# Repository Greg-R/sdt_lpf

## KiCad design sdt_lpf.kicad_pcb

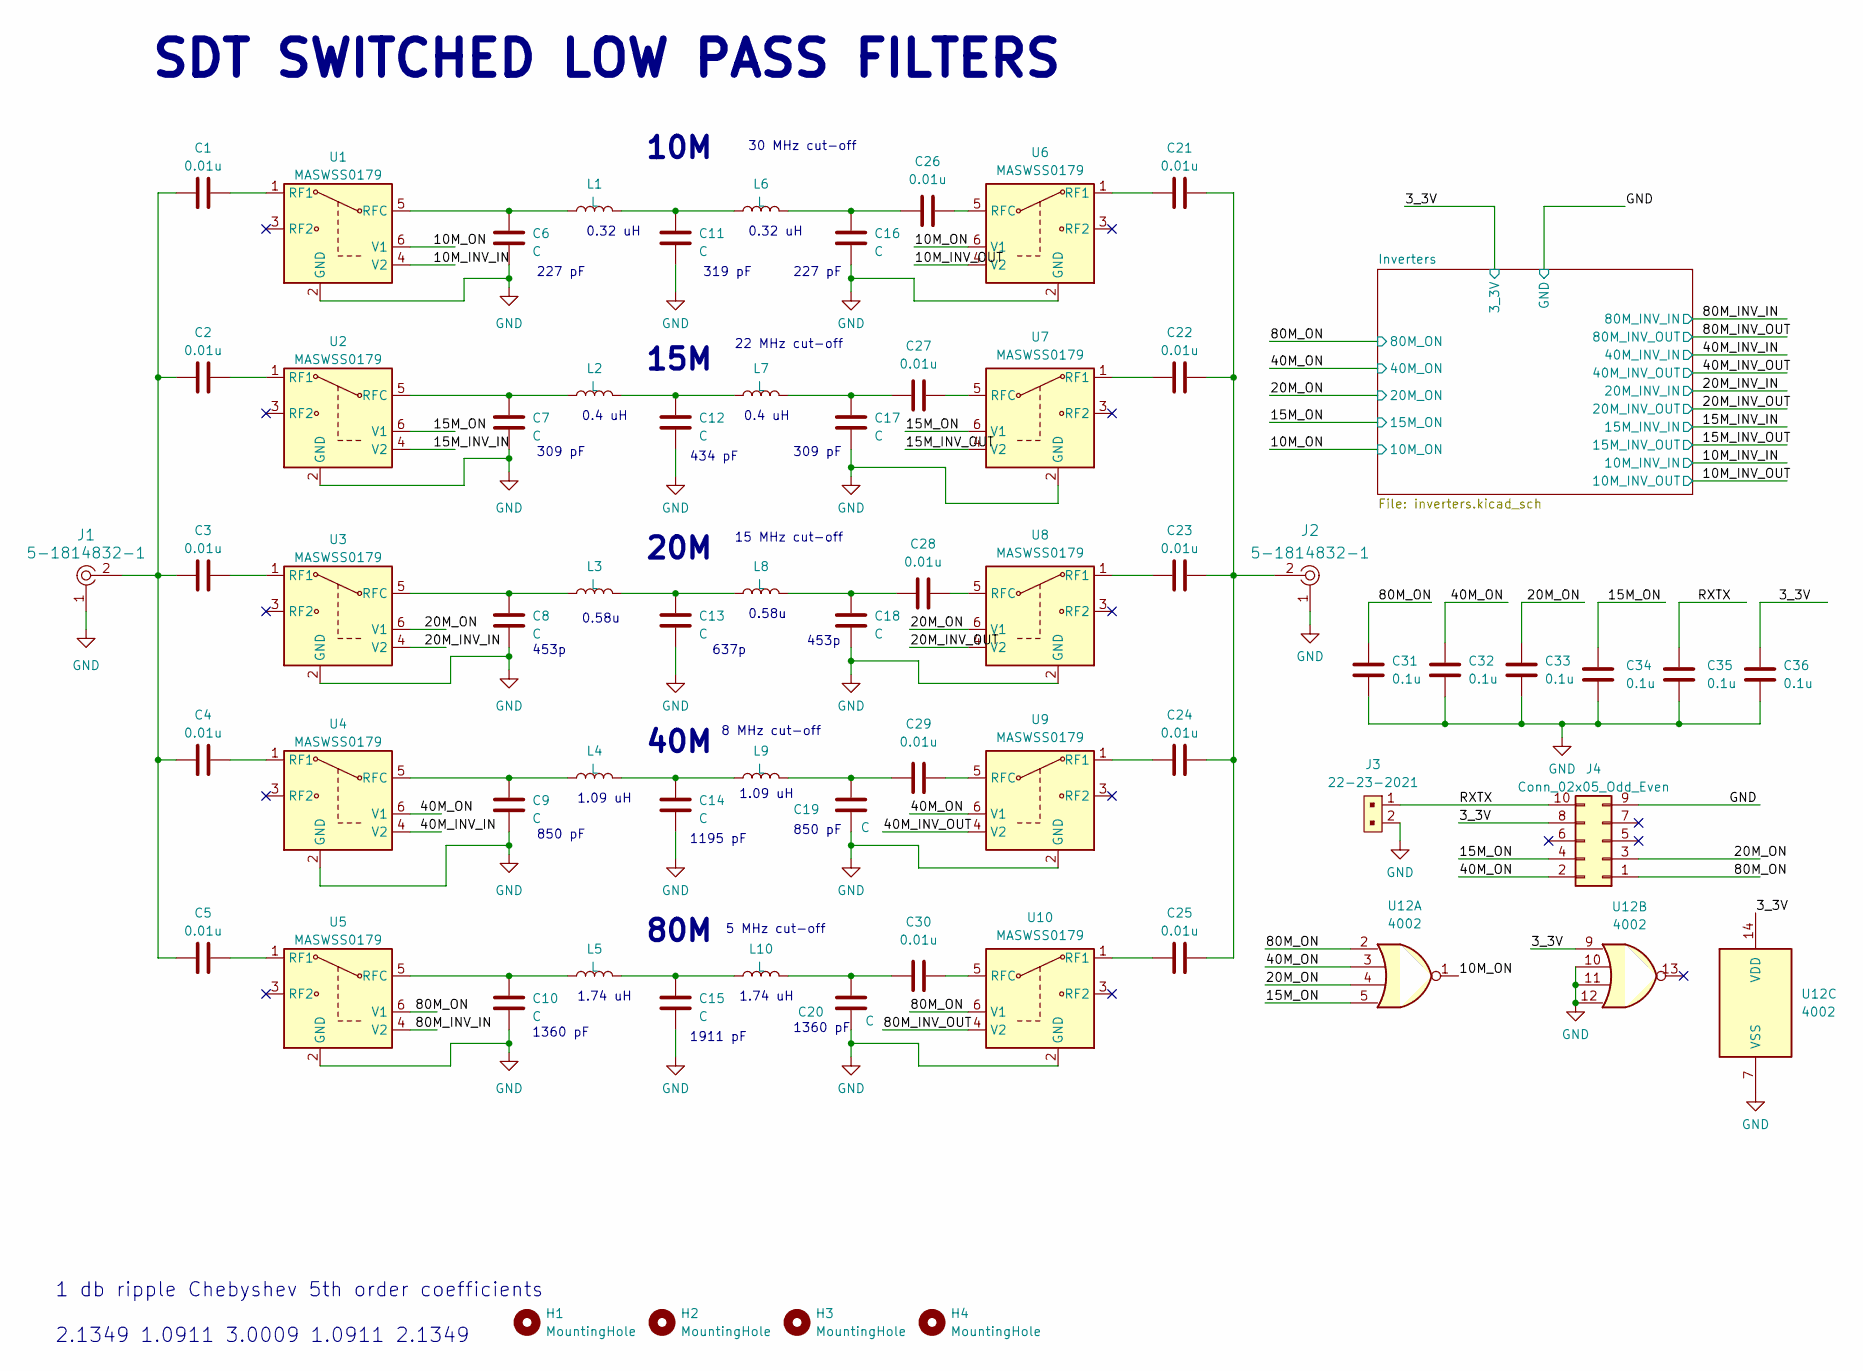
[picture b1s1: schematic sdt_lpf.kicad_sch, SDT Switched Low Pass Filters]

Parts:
C1, C2, C3, C4, C5, C21, C22, C23, C24, C25, C26, C27, C28, C29, C30: 0.01u; C_1206_3216Metric
C6, C7, C8, C9, C10, C11, C12, C13, C14, C15, C16, C17, C18, C19, C20: C; C_1206_3216Metric
C31, C32, C33, C34, C35, C36: 0.1u; C_1206_3216Metric
H1, H2, H3, H4: MountingHole; MountingHole_3.2mm_M3
J1, J2: 5-1814832-1; RF_SMA_Vertical_5-1814832-1; MPN 5-1814832-1; Digi-Key_PN A97594-ND
J3: 22-23-2021; PinHeader_1x2_P2.54mm_Drill1.02mm; MPN 22-23-2021; Digi-Key_PN WM4200-ND
J4: Conn_02x05_Odd_Even; IDC-Header_2x05_P2.54mm_Vertical
L1, L2, L3, L4, L5, L6, L7, L8, L9, L10: L; Toroid_SMD
U1, U2, U3, U4, U5, U6, U7, U8, U9, U10: MASWSS0179; SOT-23-6
U12: 4002; SOIC-14_3.9x8.7mm_P1.27mm

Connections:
/3_3V: C36.2, J4.8, U12.9, U12.14 (VDD); also elsewhere on the board
/10M_INV_IN: U1.4 (V2); also elsewhere on the board
/10M_INV_OUT: U6.4 (V2); also elsewhere on the board
/10M_ON: U1.6 (V1), U6.6 (V1), U12.1; also elsewhere on the board
/15M_INV_IN: U2.4 (V2); also elsewhere on the board
/15M_INV_OUT: U7.4 (V2); also elsewhere on the board
/15M_ON: C34.2, J4.4, U2.6 (V1), U7.6 (V1), U12.5; also elsewhere on the board
/20M_INV_IN: U3.4 (V2); also elsewhere on the board
/20M_INV_OUT: U8.4 (V2); also elsewhere on the board
/20M_ON: C33.2, J4.3, U3.6 (V1), U8.6 (V1), U12.4; also elsewhere on the board
/40M_INV_IN: U4.4 (V2); also elsewhere on the board
/40M_INV_OUT: U9.4 (V2); also elsewhere on the board
/40M_ON: C32.2, J4.2, U4.6 (V1), U9.6 (V1), U12.3; also elsewhere on the board
/80M_INV_IN: U5.4 (V2); also elsewhere on the board
/80M_INV_OUT: U10.4 (V2); also elsewhere on the board
/80M_ON: C31.2, J4.1, U5.6 (V1), U10.6 (V1), U12.2; also elsewhere on the board
/RXTX: C35.2, J3.1, J4.10
GND: C6.2, C7.2, C8.2, C9.2, C10.2, C11.2, C12.2, C13.2, C14.2, C15.2, C16.2, C17.2, C18.2, C19.2, C20.2, C31.1, C32.1, C33.1, C34.1, C35.1, C36.1, J1.1, J2.1, J3.2, J4.9, U1.2 (GND), U2.2 (GND), U3.2 (GND), U4.2 (GND), U5.2 (GND), U6.2 (GND), U7.2 (GND), U8.2 (GND), U9.2 (GND), U10.2 (GND), U12.7 (VSS), U12.10, U12.11, U12.12; also elsewhere on the board
unnamed: C1.1, C2.1, C3.1, C4.1, C5.1, J1.2
unnamed: C11.1, L1.2, L6.1
unnamed: C12.1, L2.2, L7.1
unnamed: C13.1, L3.2, L8.1
unnamed: C14.1, L4.2, L9.1
unnamed: C15.1, L5.2, L10.1
unnamed: C16.1, C26.1, L6.2
unnamed: C17.1, C27.1, L7.2
unnamed: C18.1, C28.1, L8.2
unnamed: C19.1, C29.1, L9.2
unnamed: C20.1, C30.1, L10.2
unnamed: C21.2, C22.2, C23.2, C24.2, C25.2, J2.2
unnamed: C1.2, U1.1 (RF1)
unnamed: C6.1, L1.1, U1.5 (RFC)
unnamed: C2.2, U2.1 (RF1)
unnamed: C7.1, L2.1, U2.5 (RFC)
unnamed: C3.2, U3.1 (RF1)
unnamed: C8.1, L3.1, U3.5 (RFC)
unnamed: C4.2, U4.1 (RF1)
unnamed: C9.1, L4.1, U4.5 (RFC)
unnamed: C5.2, U5.1 (RF1)
unnamed: C10.1, L5.1, U5.5 (RFC)
unnamed: C21.1, U6.1 (RF1)
unnamed: C26.2, U6.5 (RFC)
unnamed: C22.1, U7.1 (RF1)
unnamed: C27.2, U7.5 (RFC)
unnamed: C23.1, U8.1 (RF1)
unnamed: C28.2, U8.5 (RFC)
unnamed: C24.1, U9.1 (RF1)
unnamed: C29.2, U9.5 (RFC)
unnamed: C25.1, U10.1 (RF1)
unnamed: C30.2, U10.5 (RFC)

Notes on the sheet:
227 pF
637p
1911 pF
1.09 uH
0.32 uH
309 pF
850 pF
0.4 uH
8 MHz cut-off
0.58u
40M
SDT SWITCHED LOW PASS FILTERS
15M
5 MHz cut-off
1 db ripple Chebyshev 5th order coefficients 2.1349 1.0911 3.0009 1.0911 2.1349
22 MHz cut-off
453p
15 MHz cut-off
80M
20M
30 MHz cut-off
1195 pF
1.74 uH
10M
1360 pF
319 pF
434 pF

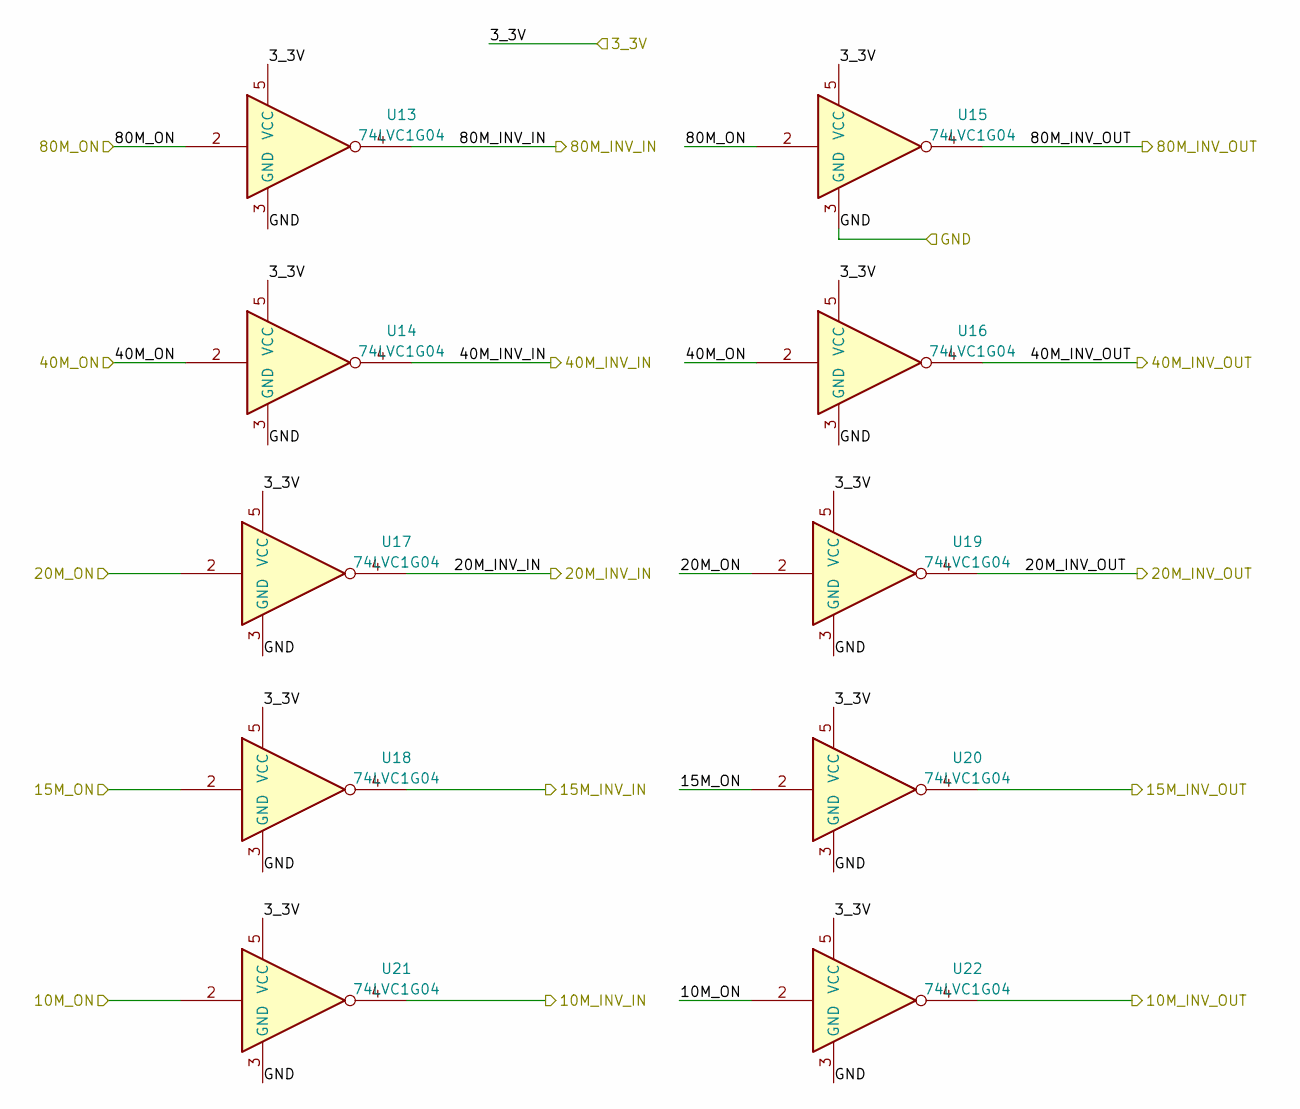
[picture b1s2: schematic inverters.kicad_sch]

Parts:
U13, U14, U15, U16, U17, U18, U19, U20, U21, U22: 74LVC1G04; SOT-353

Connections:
/3_3V: U13.5 (VCC), U14.5 (VCC), U15.5 (VCC), U16.5 (VCC), U17.5 (VCC), U18.5 (VCC), U19.5 (VCC), U20.5 (VCC), U21.5 (VCC), U22.5 (VCC); also elsewhere on the board
/10M_INV_IN: U21.4; also elsewhere on the board
/10M_INV_OUT: U22.4; also elsewhere on the board
/10M_ON: U21.2, U22.2; also elsewhere on the board
/15M_INV_IN: U18.4; also elsewhere on the board
/15M_INV_OUT: U20.4; also elsewhere on the board
/15M_ON: U18.2, U20.2; also elsewhere on the board
/20M_INV_IN: U17.4; also elsewhere on the board
/20M_INV_OUT: U19.4; also elsewhere on the board
/20M_ON: U17.2, U19.2; also elsewhere on the board
/40M_INV_IN: U14.4; also elsewhere on the board
/40M_INV_OUT: U16.4; also elsewhere on the board
/40M_ON: U14.2, U16.2; also elsewhere on the board
/80M_INV_IN: U13.4; also elsewhere on the board
/80M_INV_OUT: U15.4; also elsewhere on the board
/80M_ON: U13.2, U15.2; also elsewhere on the board
GND: U13.3 (GND), U14.3 (GND), U15.3 (GND), U16.3 (GND), U17.3 (GND), U18.3 (GND), U19.3 (GND), U20.3 (GND), U21.3 (GND), U22.3 (GND); also elsewhere on the board

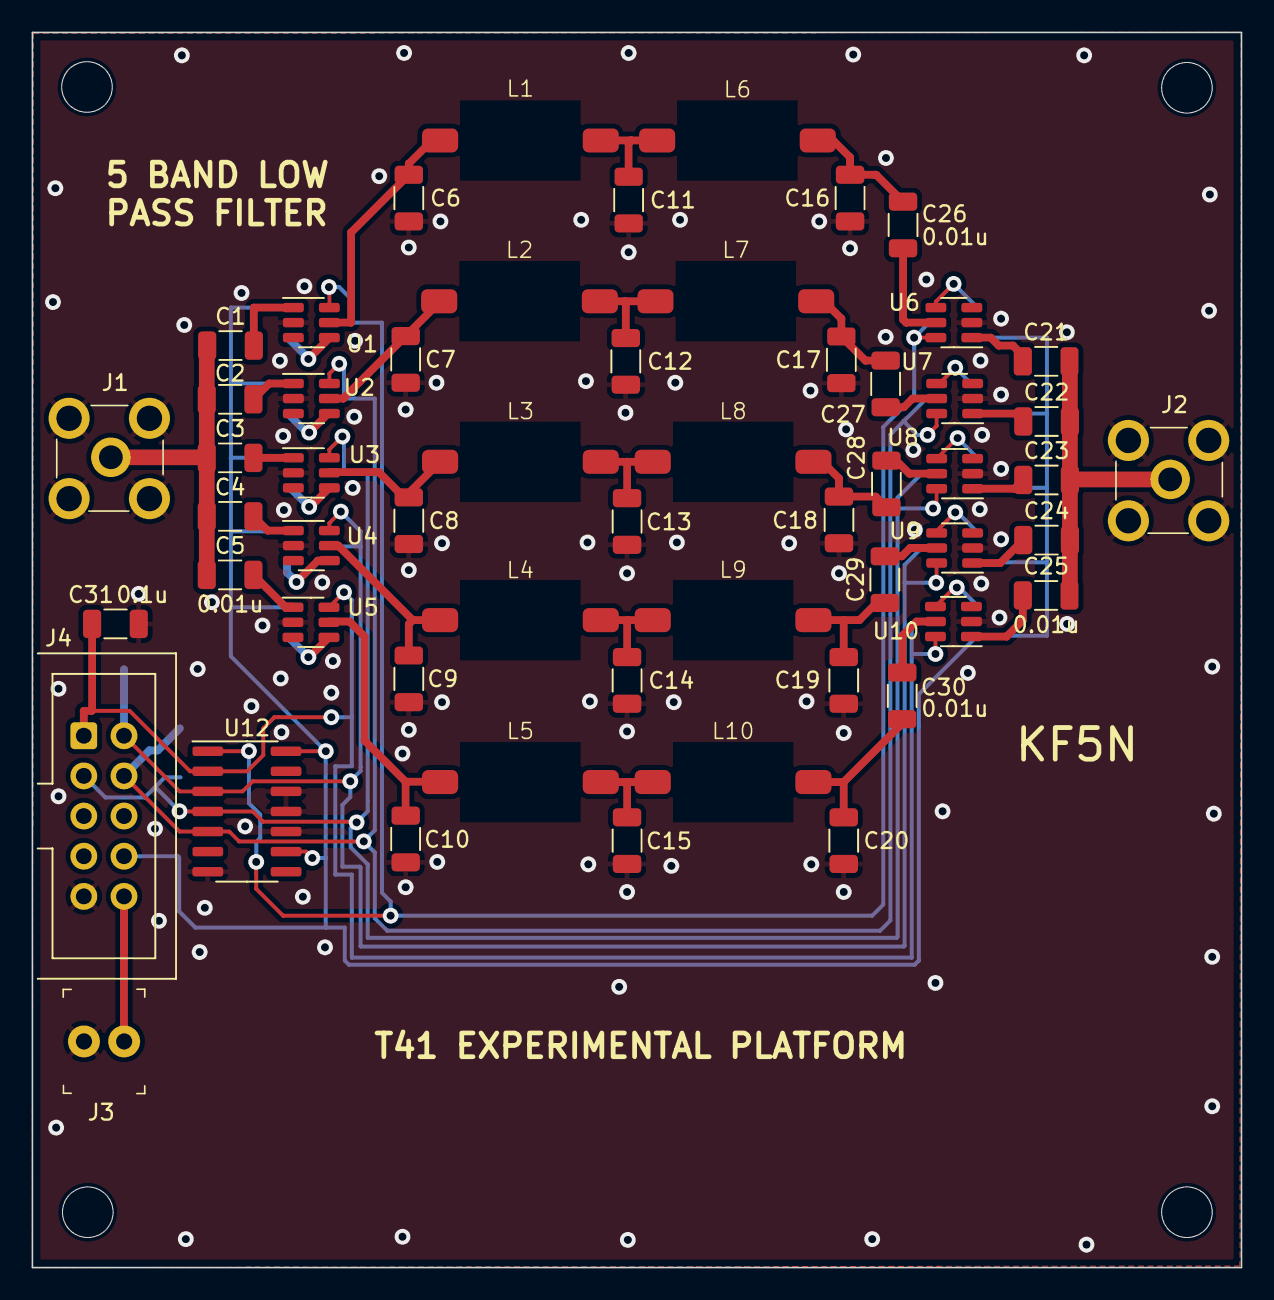
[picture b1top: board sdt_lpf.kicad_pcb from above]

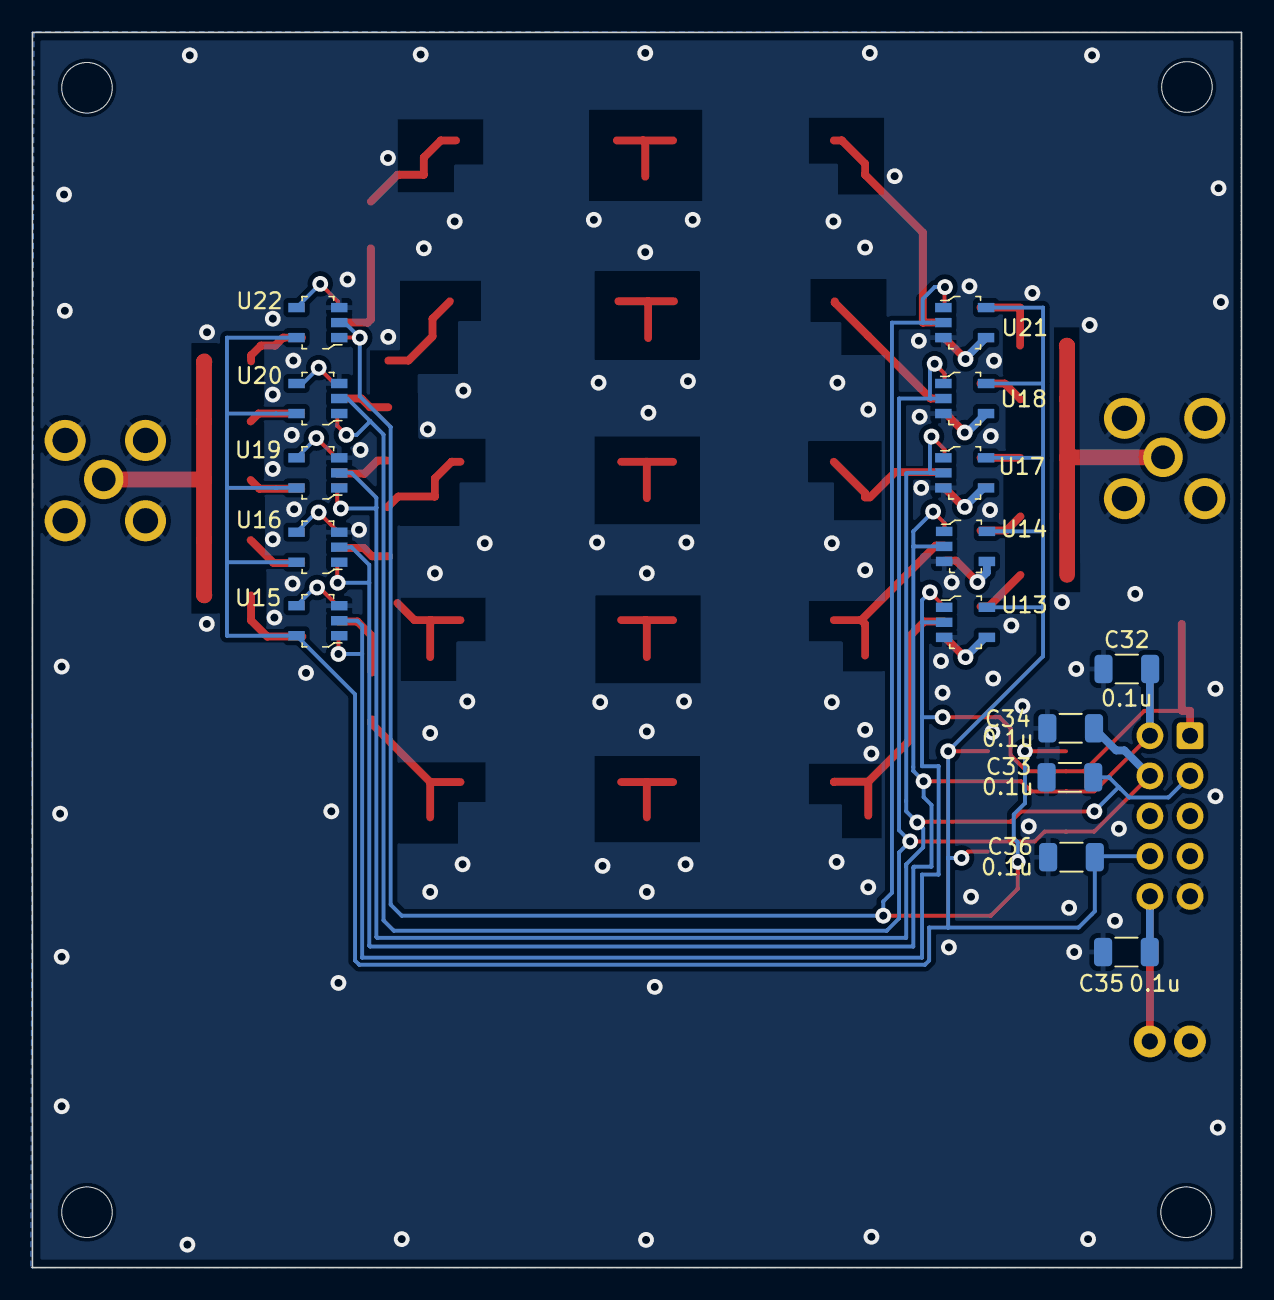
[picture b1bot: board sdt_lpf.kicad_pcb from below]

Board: 2 copper layers, 76.5 x 78.1 mm, 75 parts (15 on the bottom side), 50 nets.

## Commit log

2023-06-05 Initial commit.
2023-06-18 Commit before SSD update.
2023-06-24 Released to PCBWay June 23.
2024-01-15 Clean-up after first prototype build.
2024-02-16 Fixed logic gate, is now NOR. Cleaned up layout.
2024-02-19 Mostly completed clean-up.
2024-02-20 Ready to release to fab.
2024-03-26 Finished adding NOR gate. Ready to release proto PCB.
